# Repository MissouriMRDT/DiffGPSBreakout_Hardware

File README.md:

# DiffGPS_Breakout_Hardware
Breakout hardware for differential GPS implementation

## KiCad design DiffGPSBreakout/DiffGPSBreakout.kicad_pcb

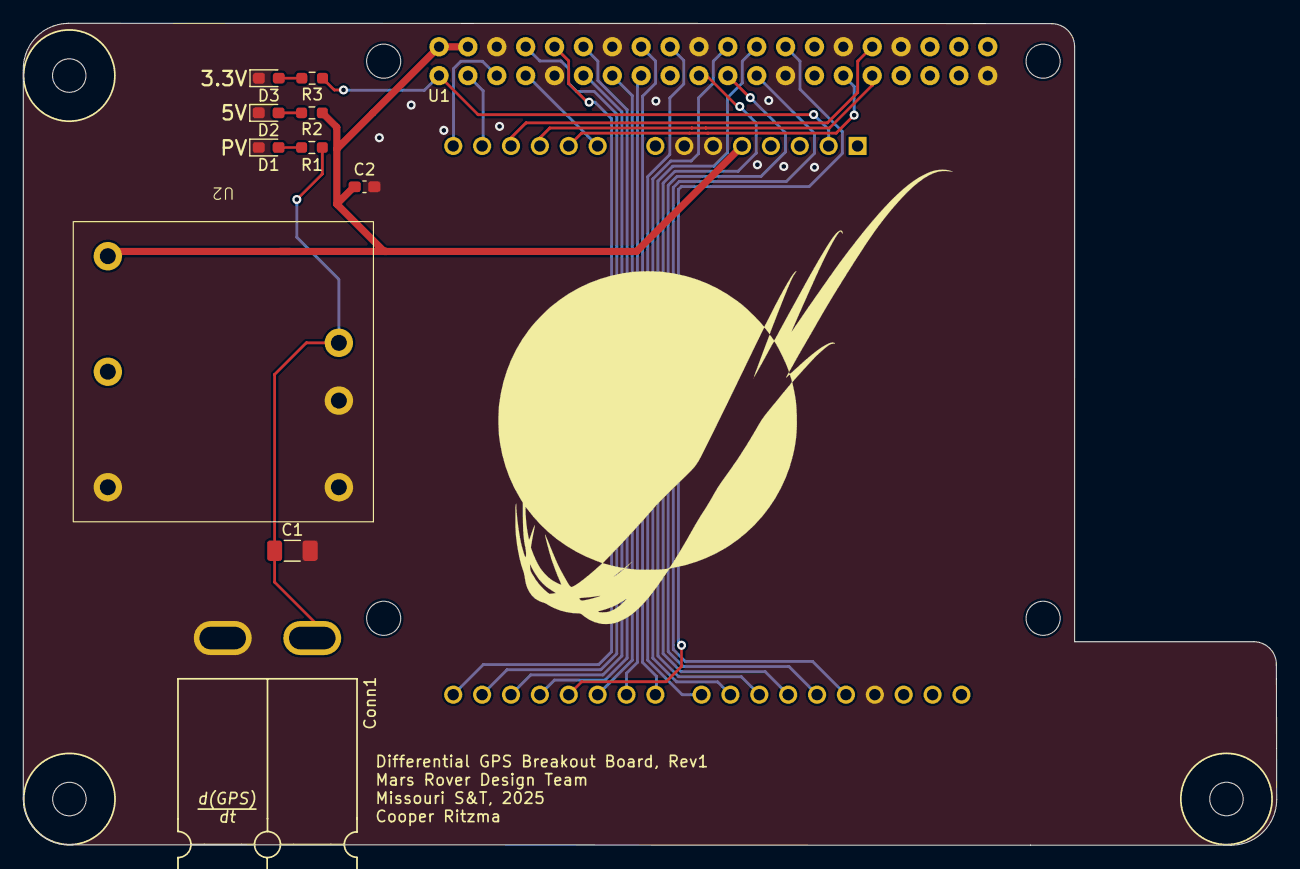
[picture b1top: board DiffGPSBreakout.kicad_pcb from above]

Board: 2 copper layers, 110.2 x 72.3 mm, 15 parts (1 on the bottom side), 27 nets.

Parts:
A1: Arduino_UNO_R3
C1: 10uF; C_1206_3216Metric_Pad1.33x1.80mm_HandSolder
C2: 10uF; C_0603_1608Metric_Pad1.08x0.95mm_HandSolder
Conn1: AndersonPP; Square_Anderson_2_H_Side_By_Side_PV
D1, D2, D3: GREEN; D_0603_1608Metric_Pad1.05x0.95mm_HandSolder
H1, H2, H3: MountingHole; 4_40_Hole_Corner
R1: 3k; R_0603_1608Metric_Pad0.98x0.95mm_HandSolder
R2: 300; R_0603_1608Metric_Pad0.98x0.95mm_HandSolder
R3: 100; R_0603_1608Metric_Pad0.98x0.95mm_HandSolder
U1: Raspberry_Pi; RaspberryPi_THT_BOTTOM
U2: PKE3311PI_Through_Hole

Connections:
+3V3: A1.2 (IOREF), R3.1, U1.1 (+3V3)
+5V: A1.5 (+5V), C2.2, R2.1, U1.2 (+5V), U1.4 (+5V), U2.4 (Vout-)
A0: A1.9 (A0), U1.7 (GP_4)
A1: A1.10 (A1), U1.29 (GP_5)
A2: A1.11 (A2), U1.31 (GP_6)
A3: A1.12 (A3), U1.32 (GP_12)
A4: A1.13 (SDA/A4), U1.3 (GP_2)
A5: A1.14 (SCL/A5), U1.5 (GP_3)
D0: A1.15 (D0/RX), U1.10 (GP_15)
D1: A1.16 (D1/TX), U1.8 (GP_14)
D2: A1.17 (D2), U1.11 (GP_17)
D3: A1.18 (D3), U1.12 (GP_18)
D4: A1.19 (D4), U1.26 (GP_7)
D5: A1.20 (D5), U1.13 (GP_27)
D6: A1.21 (D6), U1.15 (GP_22)
D7: A1.22 (D7), U1.16 (GP_23)
D8: A1.23 (D8), U1.18 (GP_24)
D9: A1.24 (D9), U1.22 (GP_25)
D10: A1.25 (D10), U1.24 (GP_8)
D11: A1.26 (D11), U1.19 (GP_10)
D12: A1.27 (D12), U1.21 (GP_9)
D13: A1.28 (D13), U1.23 (GP_11)
GND: A1.6 (GND), A1.7 (GND), A1.29 (GND), C1.2, C2.1, Conn1.1 (GND), D1.1 (K), D2.1 (K), D3.1 (K), U1.6 (GND), U1.9 (GND), U1.14 (GND), U1.20 (GND), U1.25 (GND), U1.30 (GND), U1.34 (GND), U1.39 (GND), U2.1 (Vin+), U2.2 (Vin-), U2.6 (Vout+)
unnamed: D1.2 (A), R1.1
unnamed: D2.2 (A), R2.2
unnamed: D3.2 (A), R3.2
VCC: C1.1, Conn1.4 (PV+), R1.2, U2.3 (On/OFF)

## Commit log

2023-05-07 Initial schematic + layout
2023-05-09 Removed 3.3V OKI
2023-05-10 Made Gerbs
2023-09-14 Started Schematic
2023-09-22 Schematic done
2023-09-25 Schematic Review
2023-10-03 Finished Layout
2023-10-15 Fixed some stuff, changed trace width
2023-10-15 Board Review - flipped arduino footprint
2023-10-18 fixed edge cuts, started traces
2023-10-18 tried to make buck converter
2023-10-18 Fixed Mistakes from Layout Review
2023-10-19 fixed symbol
2023-10-19 fixed layout
2023-10-20 added mrdt logo
2023-10-20 very minor changes
2023-10-20 updated Pi symbol, fixed various things
2023-10-23 minor changes
2023-10-31 finished GERBS
2023-11-08 Changed and moved capacitor
2023-11-08 changed capacitor
2023-11-16 Generated STEP File
2024-10-03 New Branch
2024-10-03 2024 copy
2024-10-22 Replaced DC-DC Converter
2024-10-29 layout copied and new footprint for dc-dc converter
2024-10-29 fixed traces
2024-10-31 Changed dc-dc converter to be accurate footprint
2024-10-31 Re-routed traces
2024-10-31 Fixed traces pt.2
2024-11-01 Generated Gerbs
2024-11-01 Saved Gerbs
2024-11-07 Changed Schematic Resistor Values
